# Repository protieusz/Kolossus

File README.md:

# Kolossus
Kolossus, a unisplit angled Katana layout with a 25mm trackball and a Panasonic roller encoder remixed from clops pcb designed by [calvin-mcd](https://github.com/calvin-mcd/clops). KLE by noelle (deer) and HA HA HA.

# PCBWay Sponsorship
The Kolossus PCB was sponsored by . Thank you PCBWay! For all your PCB prototype prints and PCBA needs you can count on PCBWay. Easy and worry free service. You submit your gerber, BOM and placement files via their website. Enter the PCB dimensions and the quantity of the prints and select the recommend shipping service, for me it is the DHL Express (DTP) for hassle free delivery.  All customs paid for. PCBWay will email you component placement clear detailed pictures for validation before soldering the rest of the PCBs.

# Description
Kolossus "...is a qazlike unibody split sub40s keyboard. The KLE and firmware is by ha ha ha which itself is inspired by a KLE from Noelle. PCB is designed by Calvin0563." Copied from Calvin's GitHub linked above. 
Kolossus is a heavy remix of clops by adding a full case to the PCB that was made from scratch using EasyEDA by extracting vital files from the Calvin0563's clops PCB files. Initially the name was Colossus but changed to Kolossus via HA HA HA's suggestion to give it a more stylist name.
Here are the list of modifications:

-Center encoder is now a 25mm trackball powered by PMW3360 sensor.

-Full enclosure case with 4 RGB cut outs.

-5mm integrated switch plate to the top case.

-Use M2 brass hot inserts 3.2mm diameter and 4mm length for the M2 screws to secure the case. I forgot how long is my M2 screws are but they should be greater than 10mm so estimated around 14.6mm. Play around with and buy multiple M2 lenght screws.

-PCB is powered by [RP2040 Zero Super Mini](https://www.aliexpress.com/item/1005007292787135.html?spm=a2g0o.order_list.order_list_main.11.46301802CibF9u) where the bottom of the mcu is flush and can sit on top of the Excelsior PCB with no issues.

-For diodes, I decided to try out the BAV70 so that I solder less diodes. I would only need to solder on 17 diodes instead of 34

-QMK code is borrowed from aki27 bally and modified the matrix to fit my Kolossus. No suppport will be given since I just copy and paste.

-Below the trackball is the optional Panasonic EVQ roller encoder or a MX switch. Case cut out was done to acoomodate the Panasonic encoder.

-Stabilizers cutout was made but was not sure about the dimensions since I have never used stabs before so a STEP case file will be included so you can cut the stab cut out further if needed. I am planning to build mine without any stabs. As always print at your own risk. No support will be given.

-Case usb c opening ~~will be~~ adjusted ~~in the future~~ to accommodate the wider USB C magnetic port. Updated bottom case on October 31, 2024.

-New full case variant designs will be printed soon. Stay tuned.

-Full production build on Oct 22, 2024.

-For Encoder soldering, the MCU will need to be soldered a little bit to the left so that there is a little bit more space for the tiny GPIO pads to be exposed for surgical soldering. The pads are tiny so I suggest a ribbon cable type cables to be use. I have not solder build the pcb with roller encoder yet. I am currently still waiting for 2x RP2040 Super mini mcus to arrive from Aliexpress.

# Disclaimer (Also copied from Calvin0563's GitHub page)

Please note that this project is a work in progress with no guarantees of a working outcome. No-one involved in this project is responsible for any usage issues that may arise. However, feel free to edit, modify and otherwise utilise these files.

# Full Production Build
Zaku 2.0 case Oct 30, 2024

Zaku Case Oct 25, 2024

# Render

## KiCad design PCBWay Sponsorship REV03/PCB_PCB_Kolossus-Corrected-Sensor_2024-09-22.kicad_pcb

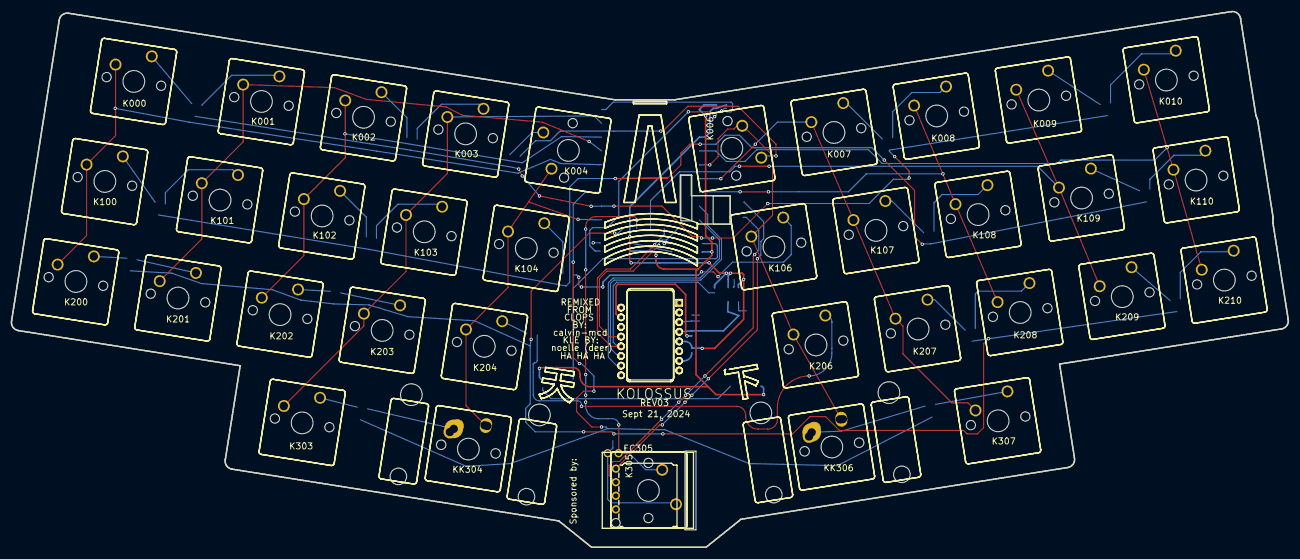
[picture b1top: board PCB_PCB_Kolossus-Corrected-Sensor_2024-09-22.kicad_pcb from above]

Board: 2 copper layers, 235.1 x 98.6 mm, 73 parts (0 on the bottom side), 69 nets.

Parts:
C17, C19, C20: 4.7uF; C0402
C18: 100nF; C0402
D000, D002, D004, D007, D008, D100, D102, D104, D107, D108, D200, D202, D204, D207, D209, D303, D305, D306: BAV70-C68978; SOT-23-3_L3.0-W1.7-P0.95-LS2.9-BR
EC305: Roll Encoder - EVQWGD001; EVQWGD001 ENCODER
ENCA: NO; PIN 1-PIN
ENCB: NO; PIN 1-PIN
K000, K001, K002, K003, K004, K006, K007, K008, K009, K010, K100, K101, K102, K103, K104, K106, K107, K108, K109, K110, K200, K201, K202, K203, K204, K206, K207, K208, K209, K210, K303, K305, K307: 100; CHERRY_MX_100_MILLMAX
KK304, KK306: 2U; MX_ALPS-2U-REVERSEDSTABILIZERS-NOLED
R10, R12, R13: 10kΩ; R0402
R11: 39Ω; R0402
R14: 15kΩ; R0402
U2: RP2040-TINY; COMM-SMD_23P-P2.54-L23.5-W18.0_RP2040-TINY
U6L: SN74LVC1T45DCKR; SC-70-6_L2.2-W1.3-P0.65-LS2.2-BR
U10: AP2127K-ADJTRG1; SOT-23-5_L3.0-W1.7-P0.95-LS2.8-BR
U11: PMW3360DM-T2QU; PMW3360DM-T2QU.PACK
U20, U21, U22, U23: SK6812MINI-E_C5149201; LED-SMD_L3.2-W2.8-TR

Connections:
+2V: C20.2, R11.2, R14.2, U10.5, U11.4
+3V3: C19.2, R10.2, R12.2, U2.21, U6L.1, U6L.5, U10.1, U10.3, U11.5
+5V: U2.23, U6L.6, U20.1, U21.1, U22.1, U23.1
COL0: K000.2, K100.2, K200.2, U2.5
COL1: K001.2, K101.2, K201.2, U2.4
COL2: K002.2, K102.2, K202.2, U2.3
COL3: K003.2, K103.2, K203.2, K303.2, U2.2
COL4: K004.2, K104.2, K204.2, KK304.2, U2.9
COL5: EC305.2, K305.2, U2.11
COL6: K006.2, K106.2, K206.2, KK306.2, U2.19
COL7: K007.2, K107.2, K207.2, K307.2, U2.18
COL8: K008.2, K108.2, K208.2, U2.17
COL9: K009.2, K109.2, K209.2, U2.12
COL10: K010.2, K110.2, K210.2, U2.20
CS: U2.14, U11.13
D303_2: D303.2, KK304.1
D306_1: D306.1, KK306.1
EC305_1: D305.1, EC305.1, K305.1
ENCA: EC305.3, ENCA.1
ENCB: EC305.4, ENCB.1
GND: C17.2, C18.2, C19.1, C20.1, EC305.5, R13.1, U2.22, U6L.2, U10.2, U11.8, U20.3, U21.3, U22.3, U23.3
K000_1: D000.1, K000.1
K001_1: D000.2, K001.1
K002_1: D002.1, K002.1
K003_1: D002.2, K003.1
K004_1: D004.1, K004.1
K006_1: D004.2, K006.1
K007_1: D007.1, K007.1
K008_1: D007.2, K008.1
K009_1: D008.1, K009.1
K010_1: D008.2, K010.1
K100_1: D100.1, K100.1
K101_1: D100.2, K101.1
K102_1: D102.1, K102.1
K103_1: D102.2, K103.1
K104_1: D104.1, K104.1
K106_1: D104.2, K106.1
K107_1: D107.1, K107.1
K108_1: D107.2, K108.1
K109_1: D108.1, K109.1
K110_1: D108.2, K110.1
K200_1: D200.1, K200.1
K201_1: D200.2, K201.1
K202_1: D202.1, K202.1
K203_1: D202.2, K203.1
K204_1: D204.1, K204.1
K206_1: D204.2, K206.1
K207_1: D207.1, K207.1
K208_1: D207.2, K208.1
K209_1: D209.1, K209.1
K210_1: D209.2, K210.1
K303_1: D303.1, K303.1
K307_1: D306.2, K307.1
MISO: R12.1, U2.13, U11.12
MOSI: U2.16, U11.11
RGB: U6L.4, U20.4
RGBMCU: U2.1, U6L.3
ROW0: D000.3, D002.3, D004.3, D007.3, D008.3, U2.8
ROW1: D100.3, D102.3, D104.3, D107.3, D108.3, U2.6
ROW2: D200.3, D202.3, D204.3, D207.3, D209.3, U2.10
ROW3: D303.3, D305.3, D306.3, U2.7
SCK: U2.15, U11.10
U10_4: R13.2, R14.1, U10.4
U11_3: C17.1, C18.1, U11.3
U11_7: R10.1, U11.7
U11_15: R11.1, U11.15
U20_2: U20.2, U21.4
U21_2: U21.2, U22.4
U23_4: U22.2, U23.4

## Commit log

2024-09-22 Match licensing to calvin-mcd
2024-09-22 Untested Production Files
2024-09-22 STEP cases
2024-09-22 STLs & 3mf
2024-09-22 PCB DXF
2024-10-22 QMK source
2024-10-31 Wider USB C for magnetic plug.
